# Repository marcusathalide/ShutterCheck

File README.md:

# ShutterCheck
Analog Camera Shutter checking tool

History:
2022-07-25: Initial version

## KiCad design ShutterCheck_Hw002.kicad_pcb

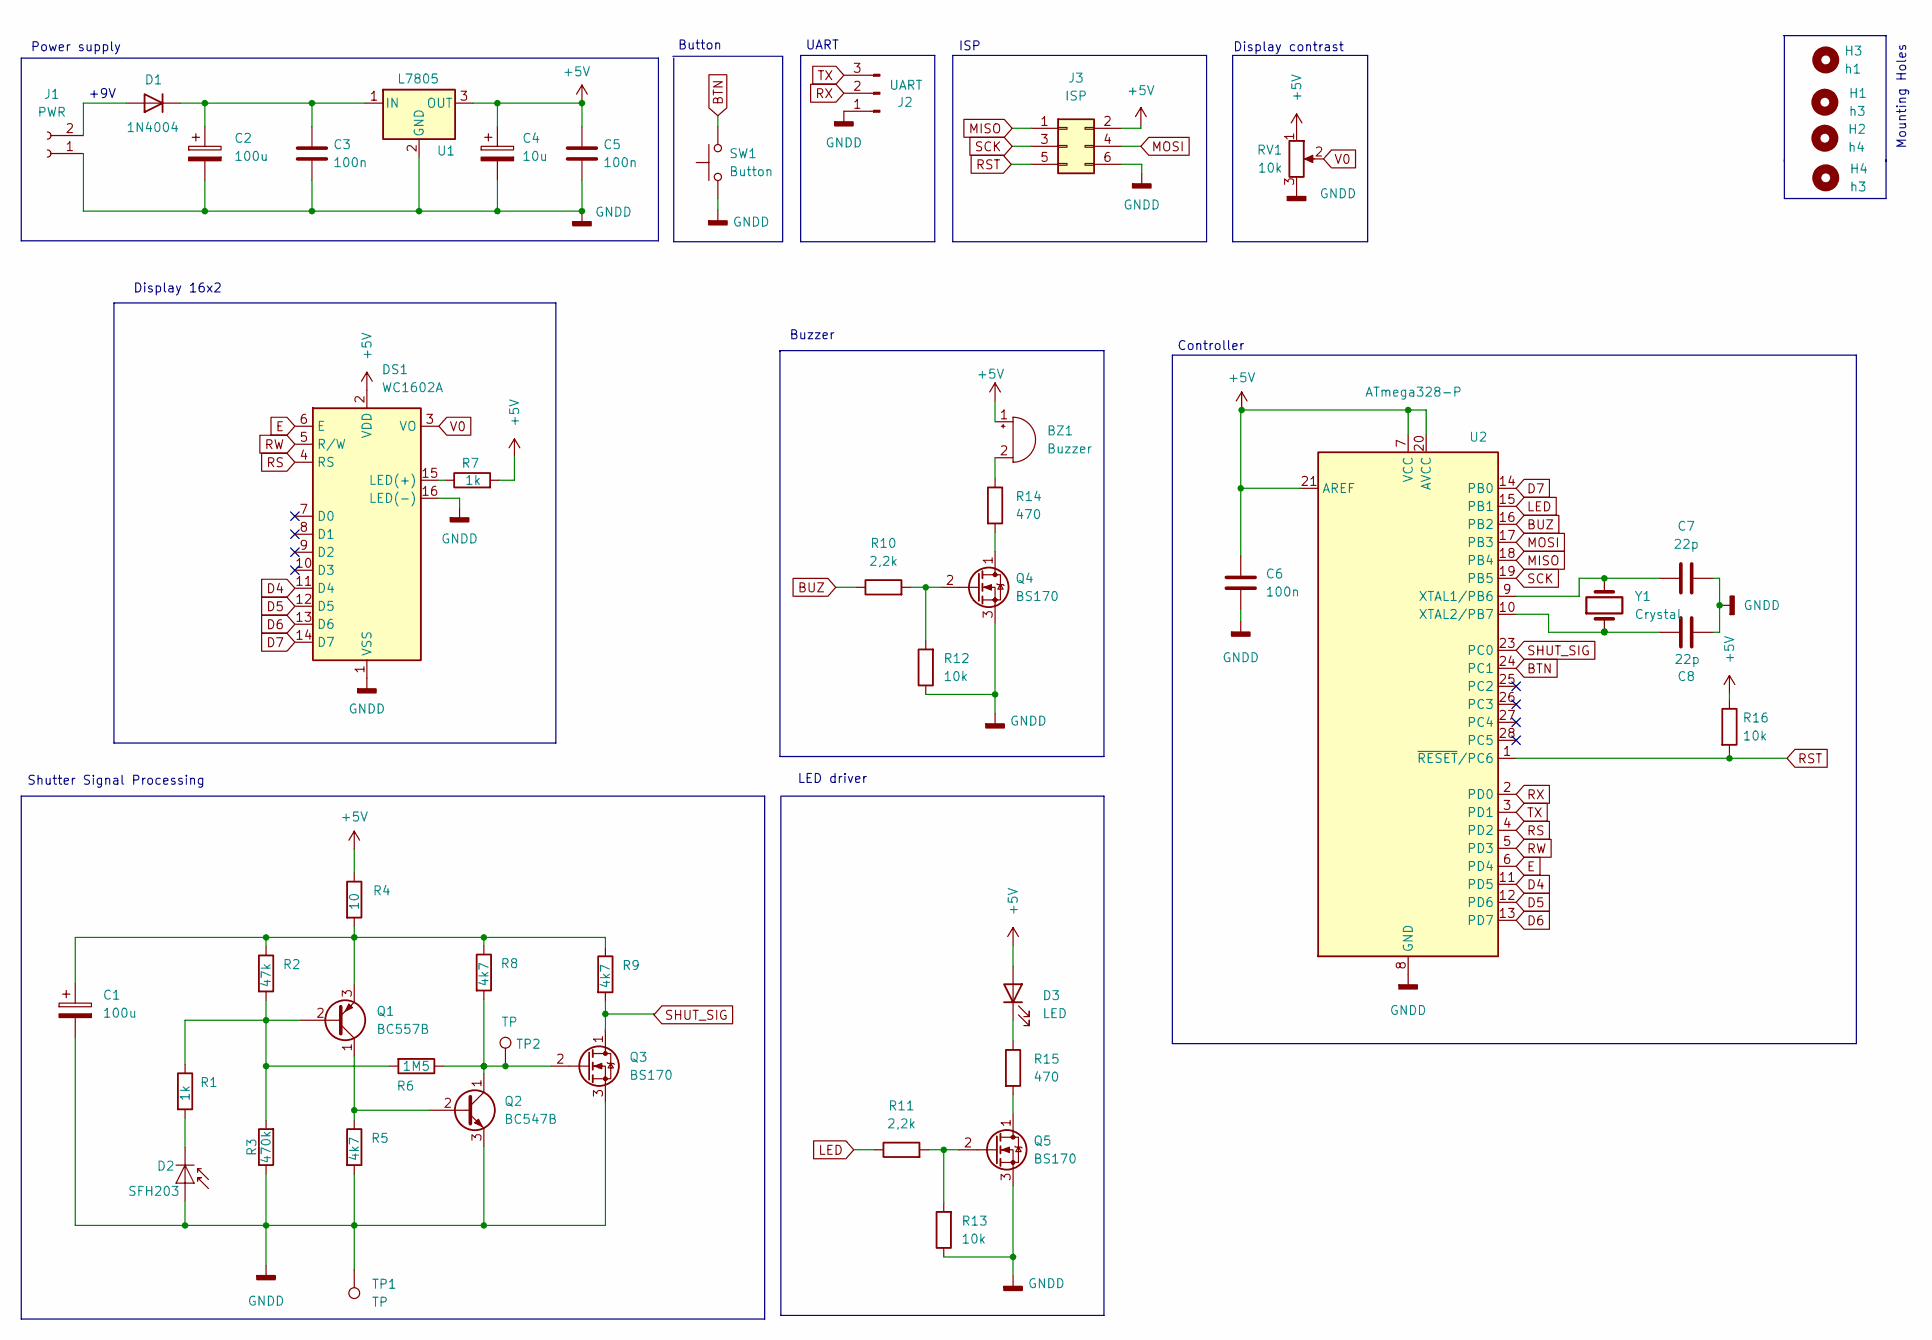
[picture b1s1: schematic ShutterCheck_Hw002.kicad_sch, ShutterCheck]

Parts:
BZ1: Buzzer; Buzzer_D14mm_H7mm_P10mm
C1, C2: 100u; CP_Radial_D6.3mm_P2.50mm
C3, C5, C6: 100n; C_Disc_D3.0mm_W1.6mm_P2.50mm
C4: 10u; CP_Radial_D5.0mm_P2.50mm
C7, C8: 22p; C_Disc_D3.0mm_W1.6mm_P2.50mm
D1: 1N4004; D_DO-41_SOD81_P10.16mm_Horizontal
D2: SFH203; LED_D5.0mm_IRGrey
D3: LED; LED_D3.0mm
DS1: WC1602A; PinSocket_1x16_P2.54mm_Vertical
H1, H4: h3; MountingHole_3.2mm_M3
H2: h4; MountingHole_3.2mm_M3
H3: h1; MountingHole_3.2mm_M3
J1: PWR; TerminalBlock_bornier-2_P5.08mm
J2: UART; PinHeader_1x03_P2.54mm_Vertical
J3: ISP; PinHeader_2x03_P2.54mm_Vertical
Q1: BC557B; TO-92_Inline_Wide
Q2: BC547B; TO-92_Inline_Wide
Q3, Q4, Q5: BS170; TO-92_Inline_Wide
R1, R7: 1k; R_Axial_DIN0204_L3.6mm_D1.6mm_P7.62mm_Horizontal
R2: 47k; R_Axial_DIN0204_L3.6mm_D1.6mm_P7.62mm_Horizontal
R3: 470k; R_Axial_DIN0204_L3.6mm_D1.6mm_P7.62mm_Horizontal
R4: 10; R_Axial_DIN0204_L3.6mm_D1.6mm_P7.62mm_Horizontal
R5, R8, R9: 4k7; R_Axial_DIN0204_L3.6mm_D1.6mm_P7.62mm_Horizontal
R6: 1M5; R_Axial_DIN0204_L3.6mm_D1.6mm_P7.62mm_Horizontal
R10, R11: 2,2k; R_Axial_DIN0204_L3.6mm_D1.6mm_P7.62mm_Horizontal
R12, R13, R16: 10k; R_Axial_DIN0204_L3.6mm_D1.6mm_P7.62mm_Horizontal
R14, R15: 470; R_Axial_DIN0204_L3.6mm_D1.6mm_P7.62mm_Horizontal
RV1: 10k; Potentiometer_Piher_PT-6-H_Horizontal
SW1: Button; PinHeader_1x02_P2.54mm_Vertical
TP1, TP2: TP; TestPoint_Pad_D2.0mm
U1: L7805; TO-220-3_Vertical
U2: ATmega328-P; DIP-28_W7.62mm
Y1: Crystal; Crystal_HC18-U_Vertical

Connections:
+5V: BZ1.1 (-), C4.1, C5.1, C6.1, D3.2 (A), DS1.2 (VDD), J3.2, R4.1, R7.2, R16.1, RV1.1, U1.3 (OUT), U2.7 (VCC), U2.20 (AVCC), U2.21 (AREF)
BTN: SW1.2, U2.24 (PC1)
BUZ: R10.1, U2.16 (PB2)
D4: DS1.11 (D4), U2.11 (PD5)
D5: DS1.12 (D5), U2.12 (PD6)
D6: DS1.13 (D6), U2.13 (PD7)
D7: DS1.14 (D7), U2.14 (PB0)
E: DS1.6 (E), U2.6 (PD4)
GNDD: C1.2, C2.2, C3.2, C4.2, C5.2, C6.2, C7.2, C8.2, D2.2 (A), DS1.1 (VSS), DS1.16 (LED(-)), J1.1, J2.1, J3.6, Q2.3 (E), Q3.3 (S), Q4.3 (S), Q5.3 (S), R3.1, R5.2, R12.1, R13.1, RV1.3, SW1.1, TP1.1, U1.2 (GND), U2.8 (GND), U2.22 (GND)
LED: R11.1, U2.15 (PB1)
MISO: J3.1, U2.18 (PB4)
MOSI: J3.4, U2.17 (PB3)
unnamed: BZ1.2 (+), R14.1
unnamed: C1.1, Q1.3 (E), R2.1, R4.2, R8.1, R9.1
unnamed: C2.1, C3.1, D1.1 (K), U1.1 (IN)
unnamed: C7.1, U2.9 (XTAL1/PB6), Y1.2
unnamed: C8.1, U2.10 (XTAL2/PB7), Y1.1
unnamed: D1.2 (A), J1.2
unnamed: D2.1 (K), R1.2
unnamed: D3.1 (K), R15.1
unnamed: DS1.15 (LED(+)), R7.1
unnamed: Q1.1 (C), Q2.2 (B), R5.1
unnamed: Q1.2 (B), R1.1, R2.2, R3.2, R6.2
unnamed: Q2.1 (C), Q3.2 (G), R6.1, R8.2, TP2.1
unnamed: Q4.1 (D), R14.2
unnamed: Q4.2 (G), R10.2, R12.2
unnamed: Q5.1 (D), R15.2
unnamed: Q5.2 (G), R11.2, R13.2
RS: DS1.4 (RS), U2.4 (PD2)
RST: J3.5, R16.2, U2.1 (~RESET/PC6)
RW: DS1.5 (R/W), U2.5 (PD3)
RX: J2.2, U2.2 (PD0)
SCK: J3.3, U2.19 (PB5)
SHUT_SIG: Q3.1 (D), R9.2, U2.23 (PC0)
TX: J2.3, U2.3 (PD1)
V0: DS1.3 (VO), RV1.2

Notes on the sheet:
ISP
UART
+9V
Button
LED driver
Power supply
Buzzer
Display 16x2
Shutter Signal Processing
Mounting Holes
Display contrast
Controller

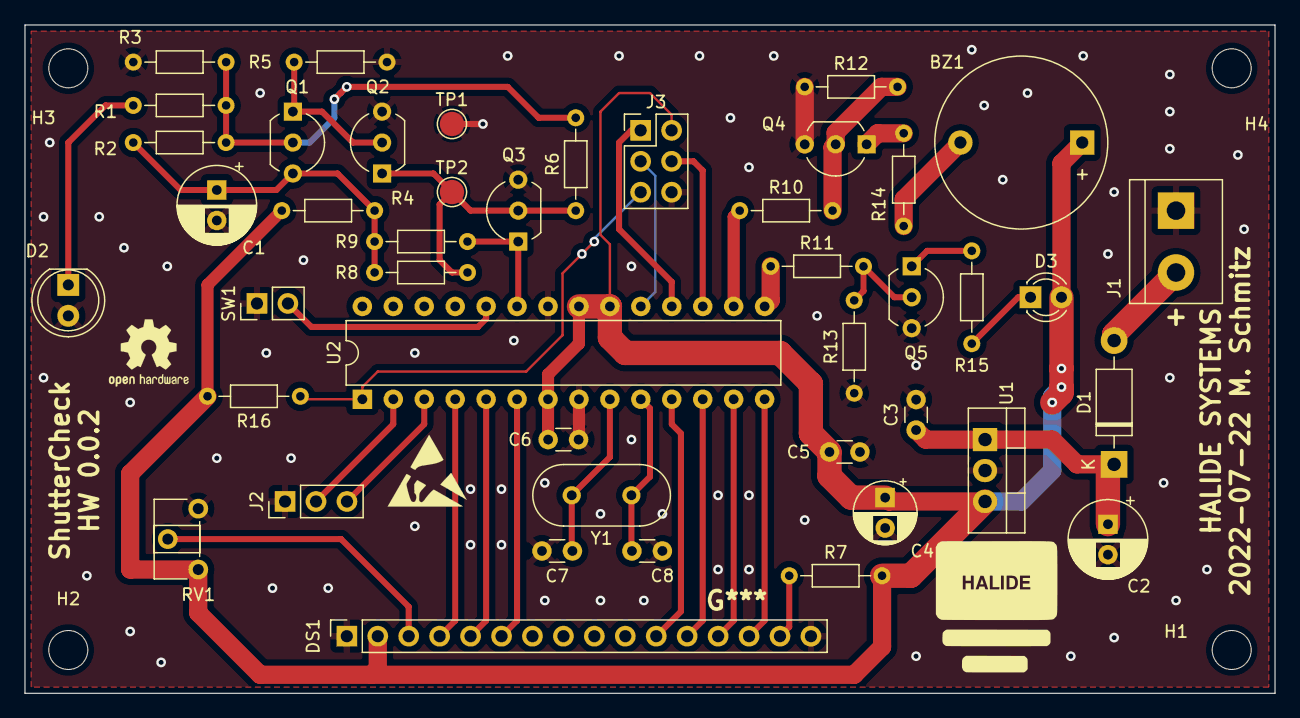
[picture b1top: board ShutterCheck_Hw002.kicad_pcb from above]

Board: 2 copper layers, 102.6 x 54.9 mm, 48 parts (0 on the bottom side), 36 nets.
